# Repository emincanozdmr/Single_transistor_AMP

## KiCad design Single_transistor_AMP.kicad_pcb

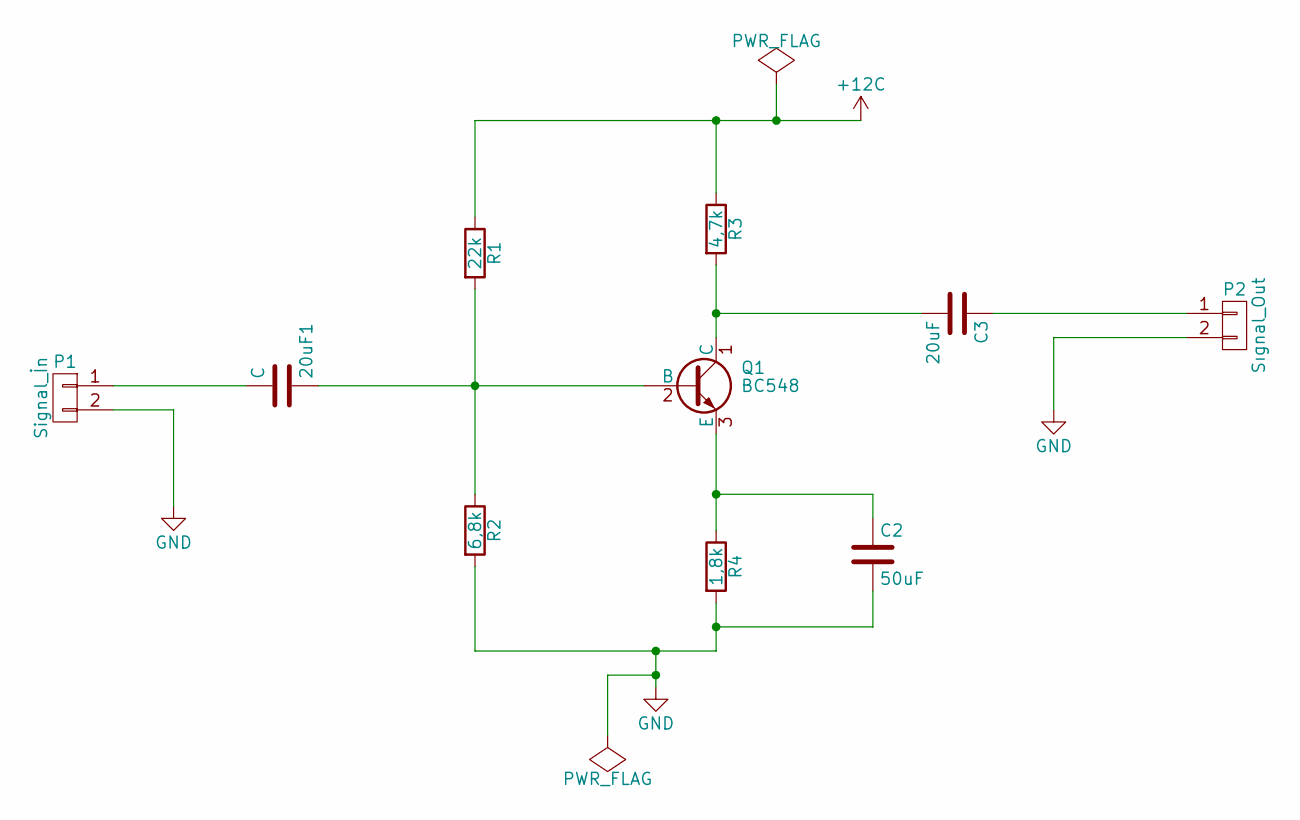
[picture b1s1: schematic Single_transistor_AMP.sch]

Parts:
20uF1: C; CP_Radial_D16.0mm_P7.50mm
C2: 50uF; CP_Axial_L21.0mm_D8.0mm_P28.00mm_Horizontal
C3: 20uF; C_Rect_L31.5mm_W9.0mm_P27.50mm_MKS4
P1: Signal_İn
P2: Sıgnal_Out
Q1: BC548; TO-92_Inline_Narrow_Oval
R1: 22k; R_Axial_DIN0207_L6.3mm_D2.5mm_P10.16mm_Horizontal
R2: 6,8k; R_Axial_DIN0207_L6.3mm_D2.5mm_P10.16mm_Horizontal
R3: 4,7k; R_Axial_DIN0207_L6.3mm_D2.5mm_P10.16mm_Horizontal
R4: 1,8k; R_Axial_DIN0207_L6.3mm_D2.5mm_P10.16mm_Horizontal

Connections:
+12C: R1.1, R3.1
GND: C2.2, P1.2, P2.2, R2.2, R4.2
unnamed: 20uF1.1, Q1.2 (B), R1.2, R2.1
unnamed: 20uF1.2, P1.1
unnamed: C2.1, Q1.3 (E), R4.1
unnamed: C3.1, P2.1
unnamed: C3.2, Q1.1 (C), R3.2

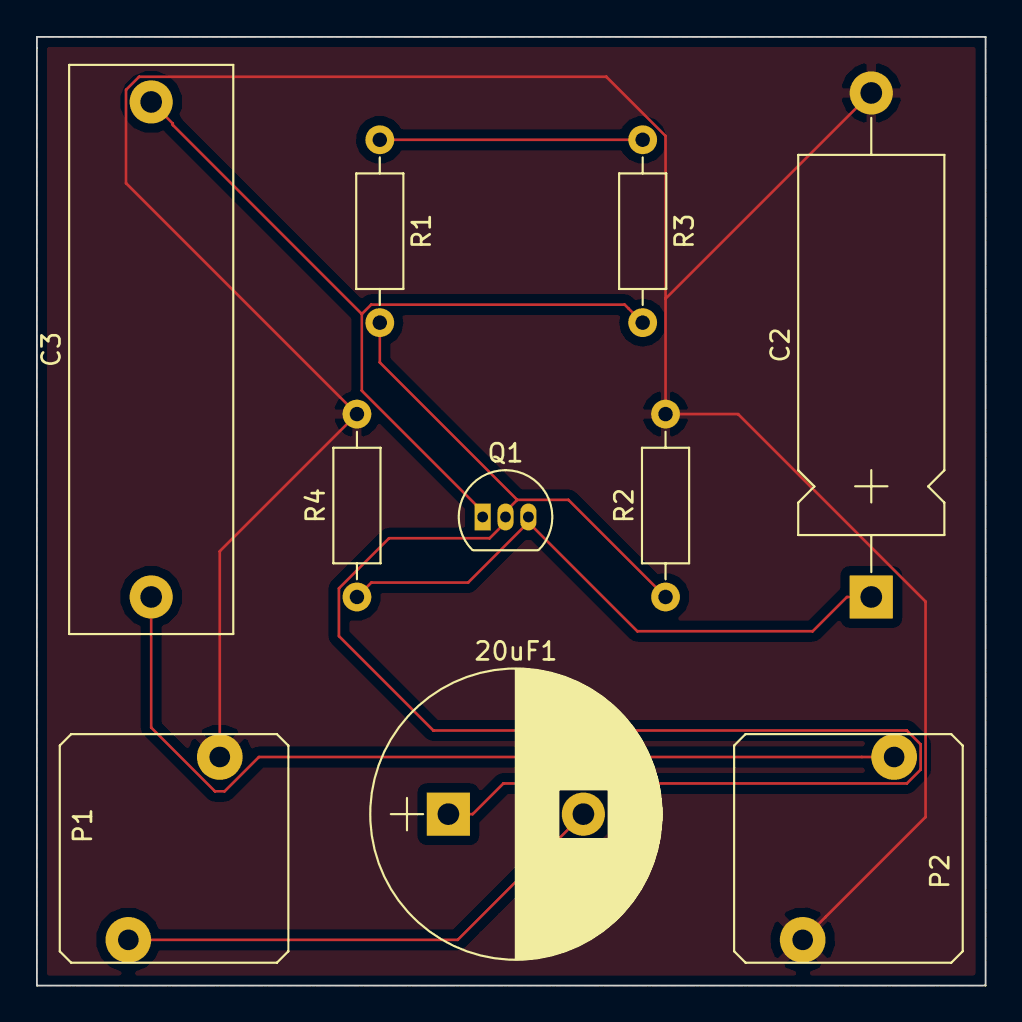
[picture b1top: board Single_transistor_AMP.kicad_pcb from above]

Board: 2 copper layers, 52.7 x 52.7 mm, 10 parts (0 on the bottom side), 7 nets.

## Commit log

2017-03-25 Single transistor AMP
2017-05-11 Single Transistor AMP added file
2017-05-24 Single Transistör AMP
2017-05-27 Single_transistor_AMP
